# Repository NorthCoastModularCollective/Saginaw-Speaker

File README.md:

# Saginaw-Speaker
Files for the Saginaw Speaker, a small, low-powered Eurorack speaker module. This module is currently *under development* and is not available for purchase or production quite yet.

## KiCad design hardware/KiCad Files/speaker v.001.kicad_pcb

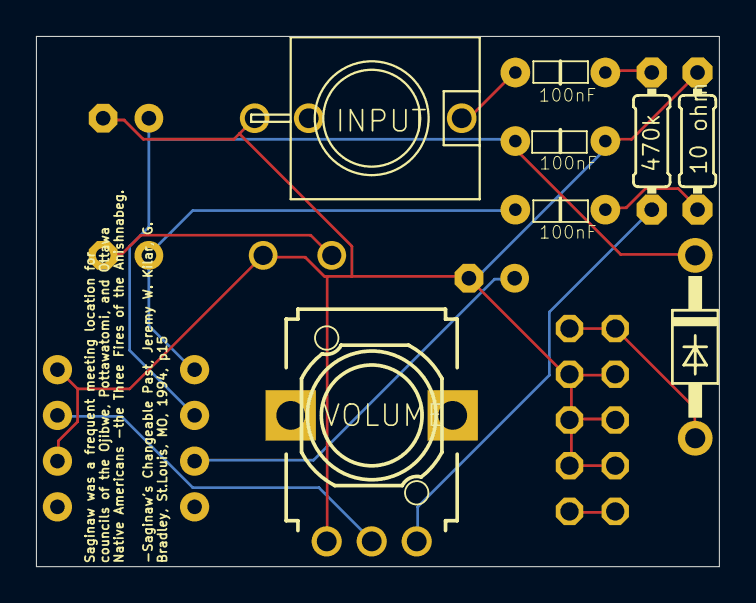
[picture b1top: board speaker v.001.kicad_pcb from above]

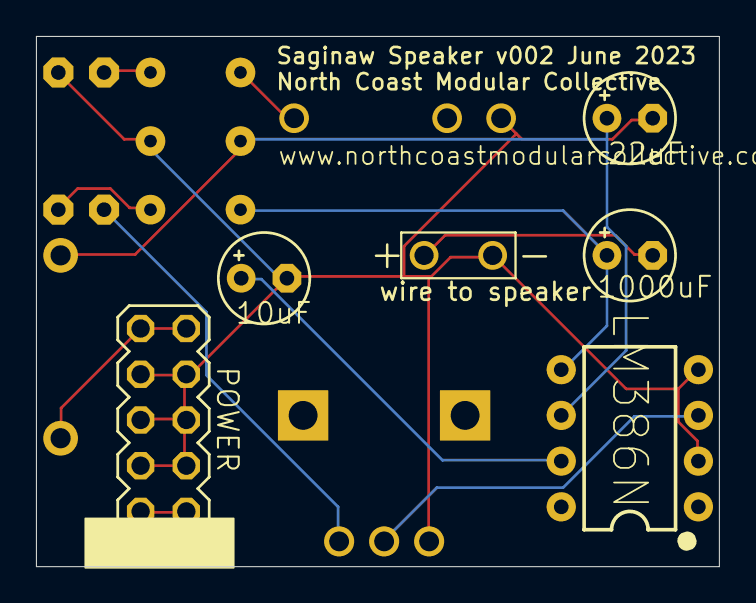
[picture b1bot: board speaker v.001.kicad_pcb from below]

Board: 2 copper layers, 37.9 x 29.5 mm, 14 parts (6 on the bottom side), 12 nets.

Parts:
C2: 22uF; E2,5-5
C3: 10uF; E2,5-5
C4: 1000uF; E2,5-5
C5, C6, C7: 100nF; SPARKFUN_CAP-PTH-5MM
D1: DO41-10
INPUT: WQP-PJ301M-12_JACK
POWER: MA05-2
R1: 10 ohm; 0204_7
R2: 470k; 0204_7
SPEAKER0: 1X02_BIG
U1: LM386N; DIP08
VOLUME: b10k; EVUFXL

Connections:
GND: C2.-, C3.-, C5.2, INPUT.P$3, POWER.3, POWER.4, POWER.5, POWER.6, POWER.7, POWER.8, R1.2, SPEAKER0.P$2, U1.2, U1.4, VOLUME.1
unnamed: R2.1, VOLUME.3
unnamed: C7.1, INPUT.P$1
unnamed: C7.2, R2.2
unnamed: U1.3, VOLUME.2
unnamed: C3.+, U1.7
unnamed: C4.+, C6.1, U1.5
unnamed: C6.2, R1.1
unnamed: C4.-, SPEAKER0.P$1
unnamed: D1.A, POWER.9, POWER.10
unnamed: POWER.1, POWER.2
V+: C2.+, C5.1, D1.C, U1.6

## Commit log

2023-06-29 Added .gitignore and build_guide folder
2023-06-29 Update README.md
    Added image of existing prototype module
2023-06-29 KiCad Initial Drop
2023-06-29 Updated PCB design
2023-06-29 added gerbers
2023-06-29 fixed gerber file date
2023-06-29 updated date
2023-06-29 Checking in new version
    Newest version of the Saginaw Speaker panel. This is an updated 8HP panel with the new module name, updated label spacing, and tweaked layout.
2023-06-29 updated kicad files
2023-06-30 Updated panel with Saginaw topo lines
2023-06-30 added .gitignore
2023-06-30 Updated topo lines, exported as DXF for import to KiCad
    Updated topo lines, exported as DXF for import to KiCad
2023-06-30 making panel
2023-07-21 Fixed panel outline rectangle
2023-07-21 updated panel
